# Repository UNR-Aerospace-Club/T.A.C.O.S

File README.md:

# T.A.C.O.S
Typical Avionics Control and Operations System

The hardware and software needed for a custom hat-based modular rocket avionics system

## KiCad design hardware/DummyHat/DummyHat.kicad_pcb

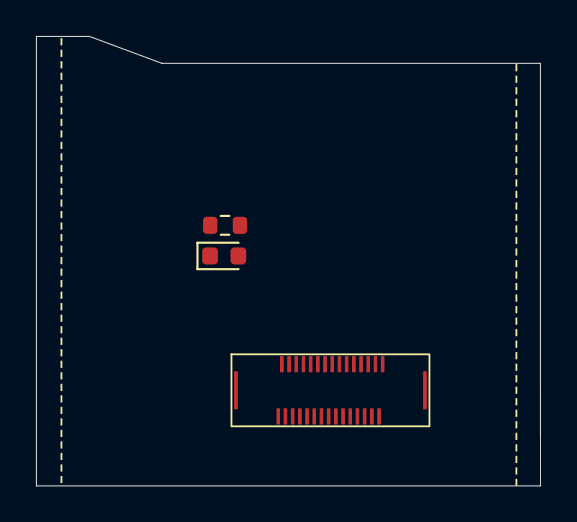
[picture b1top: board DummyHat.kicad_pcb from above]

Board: 2 copper layers, 28.0 x 25.0 mm, 4 parts (1 on the bottom side), 33 nets, no tracks yet.

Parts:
D1: LED; LED_0603_1608Metric
J1, J2: Conn_02x16_Top_Bottom; FSB5 Series 0.40 mm Pitch Floating SlimStack Board-to-Board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
R1: R; R_0603_1608Metric

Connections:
CONN_0: D1.2 (A), J1.1, J2.16
CONN_1: J1.2, J2.17
CONN_2: J1.3, J2.18
CONN_3: J1.4, J2.19
CONN_4: J1.5, J2.20
CONN_5: J1.6, J2.21
CONN_6: J1.7, J2.22
CONN_7: J1.8, J2.23
CONN_8: J1.9, J2.24
CONN_9: J1.10, J2.25
CONN_10: J1.11, J2.26
CONN_11: J1.12, J2.27
CONN_12: J1.13, J2.28
CONN_13: J1.14, J2.29
CONN_14: J1.15, J2.30
CONN_15: J1.16, J2.1
CONN_16: J1.17, J2.2
CONN_17: J1.18, J2.3
CONN_18: J1.19, J2.4
CONN_19: J1.20, J2.5
CONN_20: J1.21, J2.6
CONN_21: J1.22, J2.7
CONN_22: J1.23, J2.8
CONN_23: J1.24, J2.9
CONN_24: J1.25, J2.10
CONN_25: J1.26, J2.11
CONN_26: J1.27, J2.12
CONN_27: J1.28, J2.13
CONN_28: J1.29, J2.14
CONN_29: J1.30, J2.15
GND: J1.32, J2.32, R1.1
unnamed: D1.1 (K), R1.2
VIN: J1.31, J2.31

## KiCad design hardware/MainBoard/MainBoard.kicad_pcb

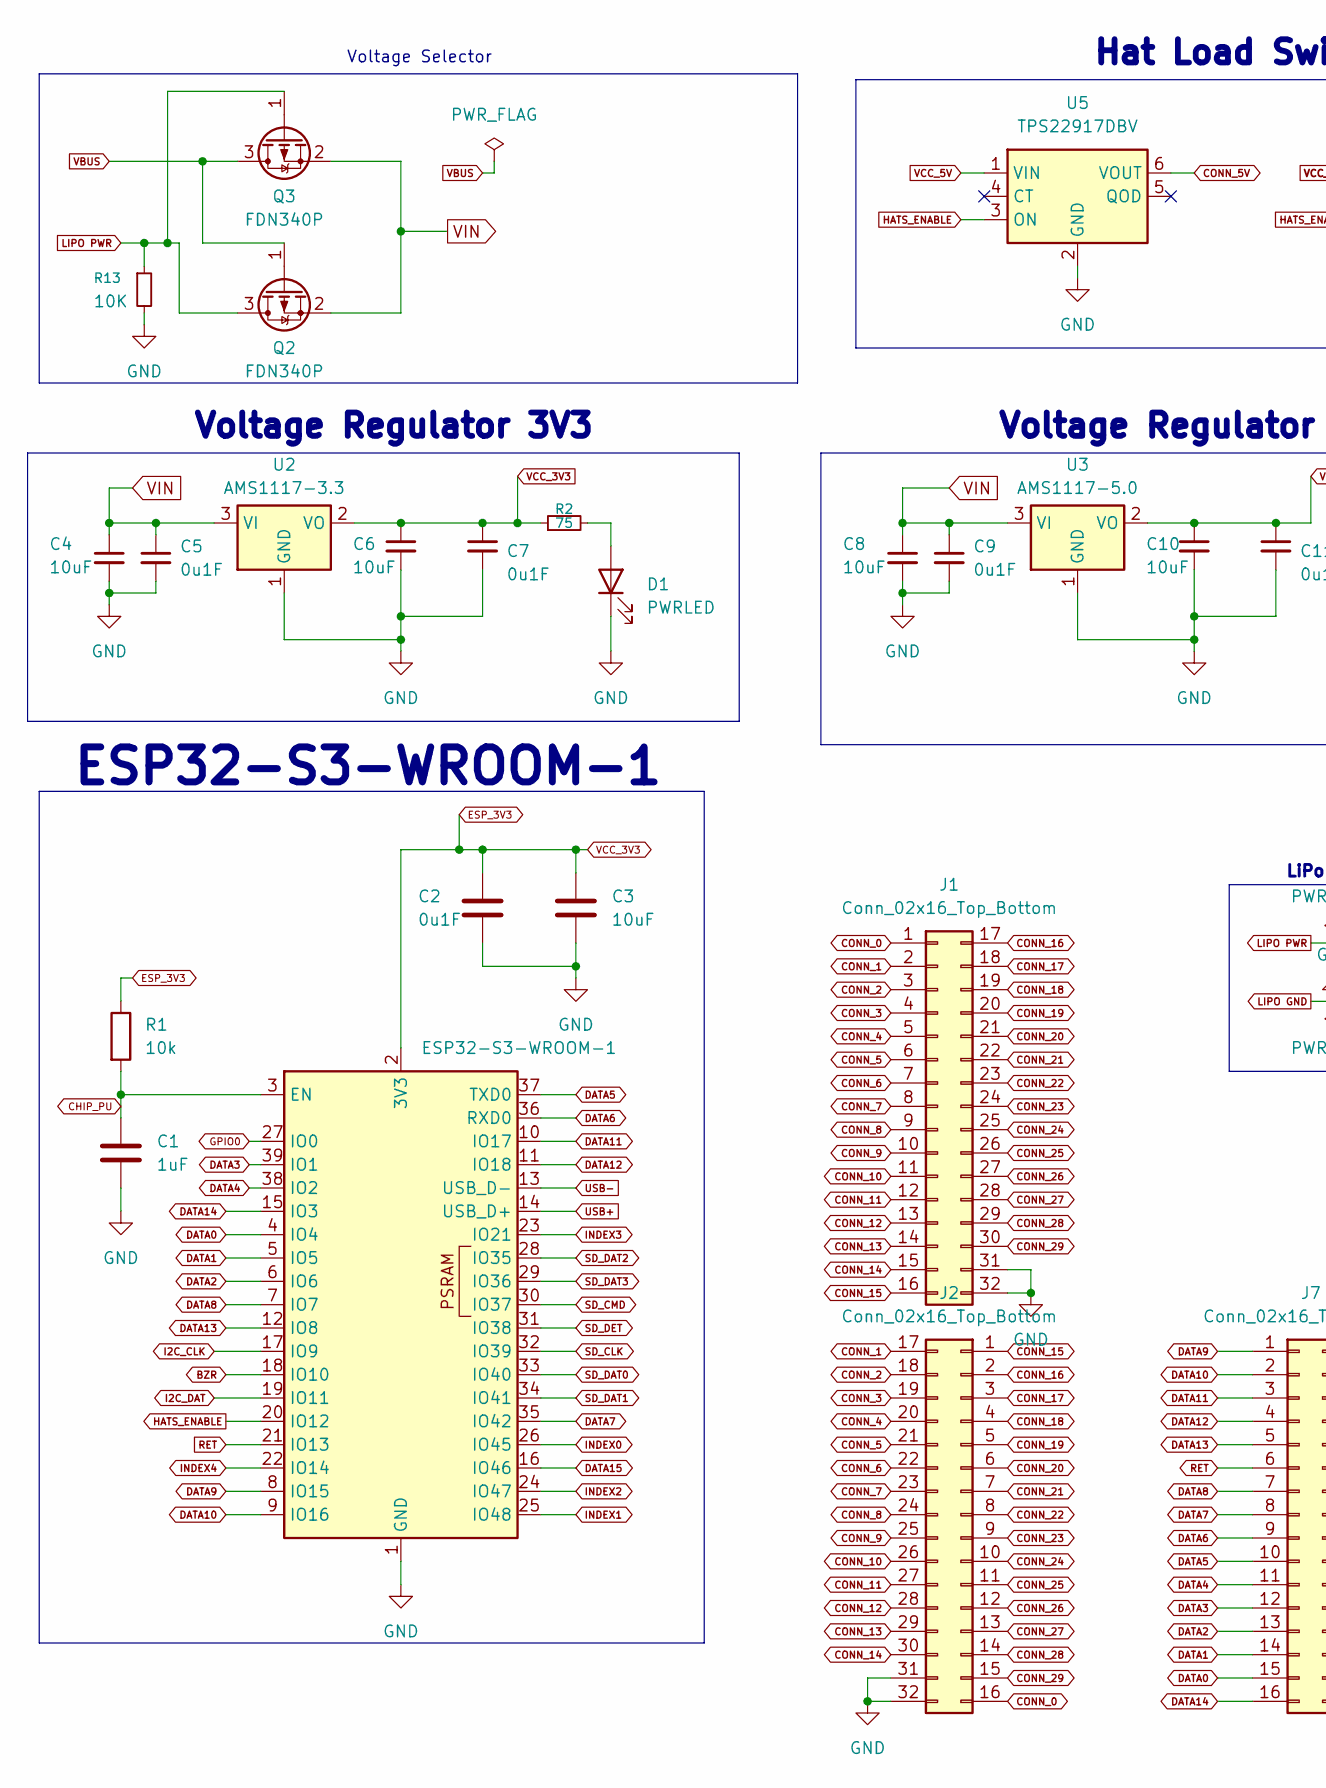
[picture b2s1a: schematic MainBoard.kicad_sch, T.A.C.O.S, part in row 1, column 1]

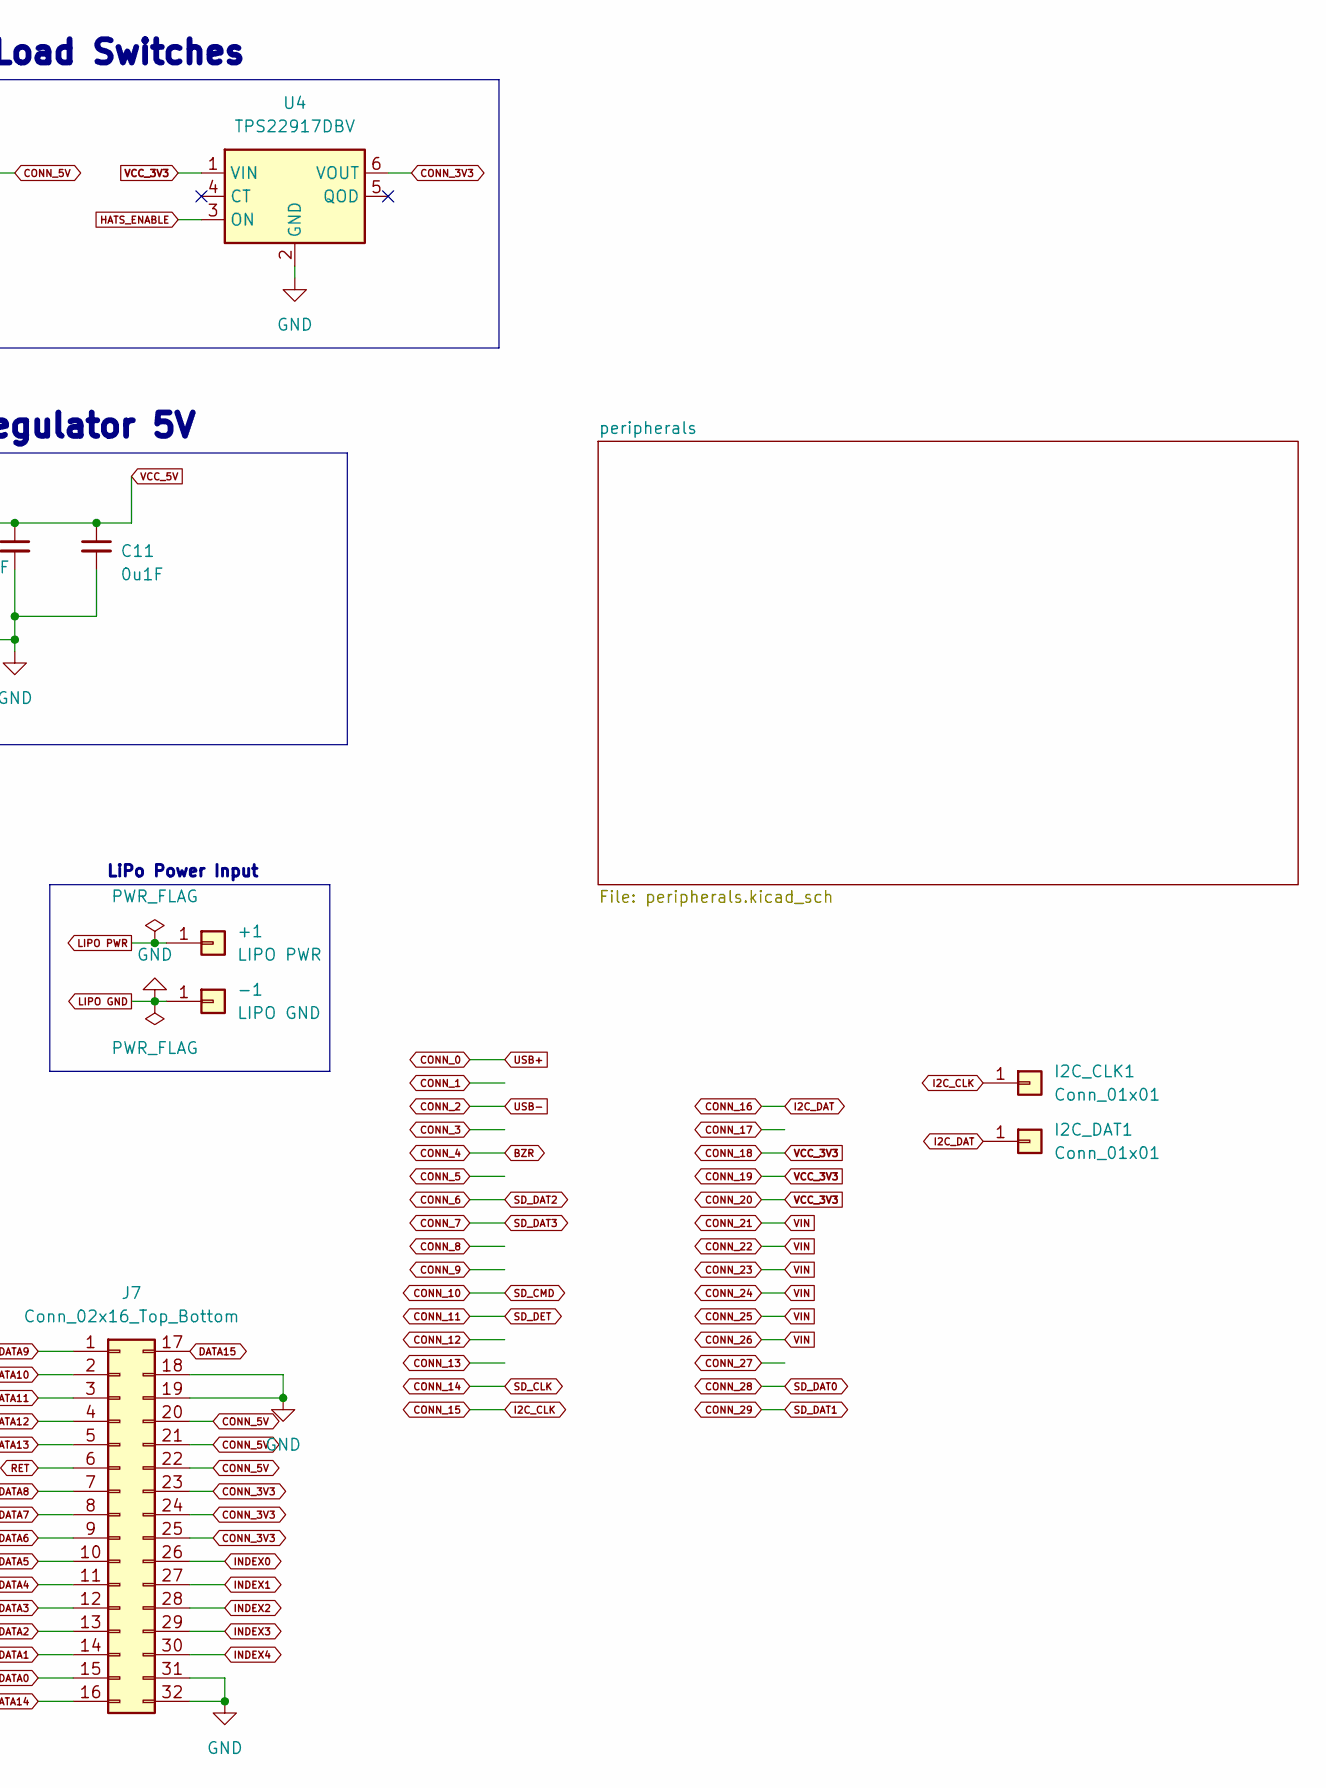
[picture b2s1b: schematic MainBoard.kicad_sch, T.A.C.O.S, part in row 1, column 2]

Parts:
+1: LIPO PWR; TestPoint_Pad_2.0x2.0mm
-1: LIPO GND; TestPoint_Pad_2.0x2.0mm
C1: 1uF; C_0603_1608Metric
C2, C5, C7, C9, C11: 0u1F; C_0402_1005Metric
C3, C4, C6, C8, C10: 10uF; C_0603_1608Metric
D1: PWRLED; LED_0603_1608Metric
I2C_CLK1, I2C_DAT1: Conn_01x01; TestPoint_Pad_1.0x1.0mm
J1, J2, J7: Conn_02x16_Top_Bottom; FSB5 Series 0.40 mm Pitch Floating SlimStack Board-to-Board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
Q2, Q3: FDN340P; SOT-23
R1: 10k; R_0603_1608Metric
R2: 75; R_0603_1608Metric
R13: 10K; R_0603_1608Metric
U1: ESP32-S3-WROOM-1; ESP32-S3-WROOM-1U
U2: AMS1117-3.3; SOT-223-3_TabPin2
U3: AMS1117-5.0; SOT-223-3_TabPin2
U4, U5: TPS22917DBV; SOT-23-6

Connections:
BZR: J1.5, J2.20, U1.18 (IO10); also elsewhere on the board
CHIP_PU: C1.1, R1.2, U1.3 (EN); also elsewhere on the board
CONN_0: J1.1, J2.16, U1.14 (USB_D+); also elsewhere on the board
CONN_1: J1.2, J2.17
CONN_2: J1.3, J2.18, U1.13 (USB_D-); also elsewhere on the board
CONN_3: J1.4, J2.19
CONN_3V3: J7.23, J7.24, J7.25, U4.6 (VOUT)
CONN_5: J1.6, J2.21
CONN_5V: J7.20, J7.21, J7.22, U5.6 (VOUT)
CONN_6: J1.7, J2.22, U1.28 (IO35); also elsewhere on the board
CONN_7: J1.8, J2.23, U1.29 (IO36); also elsewhere on the board
CONN_8: J1.9, J2.24
CONN_9: J1.10, J2.25
CONN_10: J1.11, J2.26, U1.30 (IO37); also elsewhere on the board
CONN_11: J1.12, J2.27, U1.31 (IO38); also elsewhere on the board
CONN_12: J1.13, J2.28
CONN_13: J1.14, J2.29
CONN_14: J1.15, J2.30, U1.32 (IO39); also elsewhere on the board
CONN_15: I2C_CLK1.1, J1.16, J2.1, U1.17 (IO9)
CONN_16: I2C_DAT1.1, J1.17, J2.2, U1.19 (IO11)
CONN_17: J1.18, J2.3
CONN_18: C2.1, C3.1, C6.1, C7.1, J1.19, J1.20, J1.21, J2.4, J2.5, J2.6, R1.1, R2.1, U1.2 (3V3), U2.2 (VO), U4.1 (VIN); also elsewhere on the board
CONN_21: C4.1, C5.1, C8.1, C9.1, J1.22, J1.23, J1.24, J1.25, J1.26, J1.27, J2.7, J2.8, J2.9, J2.10, J2.11, J2.12, Q2.2 (S), Q3.2 (S), U2.3 (VI), U3.3 (VI)
CONN_27: J1.28, J2.13
CONN_28: J1.29, J2.14, U1.33 (IO40); also elsewhere on the board
CONN_29: J1.30, J2.15, U1.34 (IO41); also elsewhere on the board
DATA0: J7.15, U1.4 (IO4)
DATA1: J7.14, U1.5 (IO5)
DATA2: J7.13, U1.6 (IO6)
DATA3: J7.12, U1.39 (IO1)
DATA4: J7.11, U1.38 (IO2)
DATA5: J7.10, U1.37 (TXD0)
DATA6: J7.9, U1.36 (RXD0)
DATA7: J7.8, U1.35 (IO42)
DATA8: J7.7, U1.7 (IO7)
DATA9: J7.1, U1.8 (IO15)
DATA10: J7.2, U1.9 (IO16)
DATA11: J7.3, U1.10 (IO17)
DATA12: J7.4, U1.11 (IO18)
DATA13: J7.5, U1.12 (IO8)
DATA14: J7.16, U1.15 (IO3)
DATA15: J7.17, U1.16 (IO46)
GPIO0: U1.27 (IO0); also elsewhere on the board
HATS_ENABLE: U1.20 (IO12), U4.3 (ON), U5.3 (ON)
INDEX0: J7.26, U1.26 (IO45)
INDEX1: J7.27, U1.25 (IO48)
INDEX2: J7.28, U1.24 (IO47)
INDEX3: J7.29, U1.23 (IO21)
INDEX4: J7.30, U1.22 (IO14)
LIPO GND: -1.1, C1.2, C2.2, C3.2, C4.2, C5.2, C6.2, C7.2, C8.2, C9.2, C10.2, C11.2, D1.1 (K), J1.31, J1.32, J2.31, J2.32, J7.18, J7.19, J7.31, J7.32, R13.2, U1.1 (GND), U1.40 (GND), U1.41 (GND), U2.1 (GND), U3.1 (GND), U4.2 (GND), U5.2 (GND); also elsewhere on the board
LIPO PWR: +1.1, Q2.3 (D), Q3.1 (G), R13.1
unnamed: D1.2 (A), R2.2
RET: J7.6, U1.21 (IO13)
VBUS: Q2.1 (G), Q3.3 (D); also elsewhere on the board
VCC_5V: C10.1, C11.1, U3.2 (VO), U5.1 (VIN)

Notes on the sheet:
Voltage Regulator 5V
ESP32-S3-WROOM-1
Voltage Regulator 3V3
Voltage Selector
LiPo Power Input
Hat Load Switches

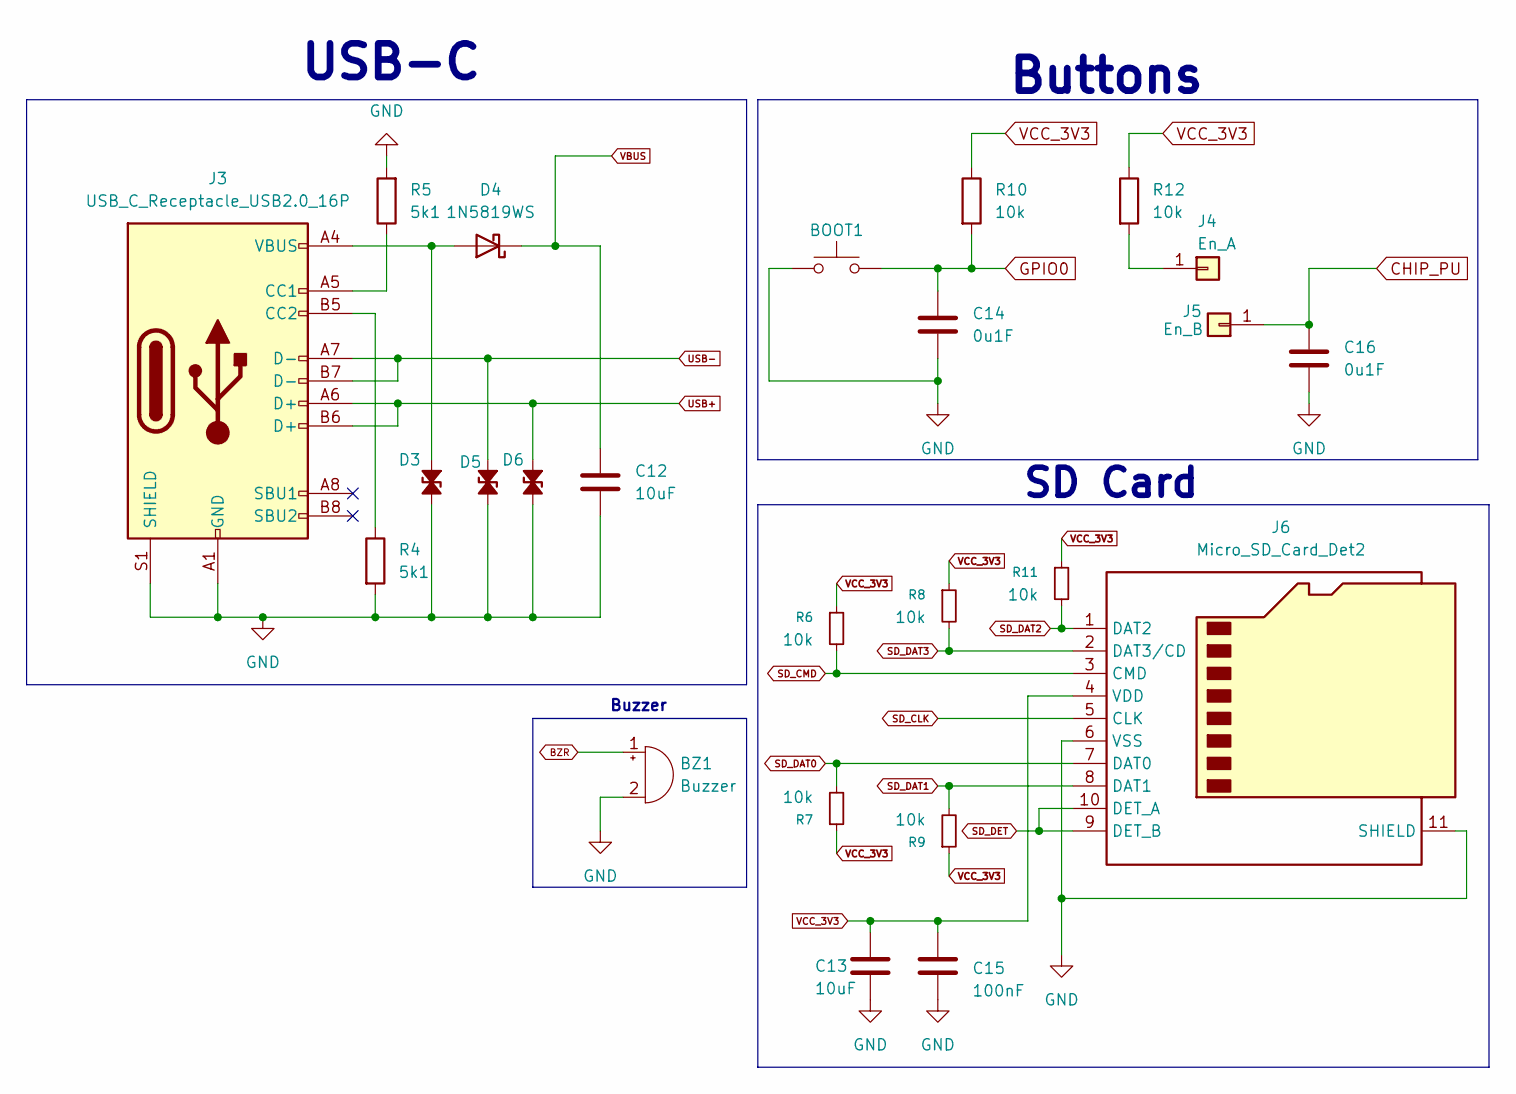
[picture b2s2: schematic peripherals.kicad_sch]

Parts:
BOOT1: RESET; SW_Push_1P1T_NO_CK_KMR2
BZ1: Buzzer; Buzzer_Murata_PKMCS0909E
C12, C13: 10uF; C_0603_1608Metric
C14, C16: 0u1F; C_0402_1005Metric
C15: 100nF; C_0402_1005Metric
D3, D5, D6: D_TVS_Small_Filled; D_0603_1608Metric
D4: 1N5819WS; D_SOD-323
J3: USB_C_Receptacle_USB2.0_16P; USB_C_Receptacle_GCT_USB4085
J4: En_A; TestPoint_Pad_1.5x1.5mm
J5: En_B; TestPoint_Pad_1.5x1.5mm
J6: Micro_SD_Card_Det2; microSD_HC_Hirose_DM3AT-SF-PEJM5
R4, R5: 5k1; R_0402_1005Metric
R6, R7, R8, R9, R10, R11, R12: 10k; R_0603_1608Metric

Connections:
BZR: BZ1.1 (+); also elsewhere on the board
CHIP_PU: C16.1, J5.1; also elsewhere on the board
CONN_0: D6.1 (A1), J3.A6 (D+), J3.B6 (D+); also elsewhere on the board
CONN_2: D5.1 (A1), J3.A7 (D-), J3.B7 (D-); also elsewhere on the board
CONN_6: J6.1 (DAT2), R11.2; also elsewhere on the board
CONN_7: J6.2 (DAT3/CD), R8.2; also elsewhere on the board
CONN_10: J6.3 (CMD), R6.2; also elsewhere on the board
CONN_11: J6.9 (DET_B), J6.10 (DET_A); also elsewhere on the board
CONN_14: J6.5 (CLK); also elsewhere on the board
CONN_18: C13.1, C15.1, J6.4 (VDD), R6.1, R7.1, R8.1, R9.1, R10.1, R11.1, R12.1; also elsewhere on the board
CONN_28: J6.7 (DAT0), R7.2; also elsewhere on the board
CONN_29: J6.8 (DAT1), R9.2; also elsewhere on the board
GPIO0: BOOT1.2, C14.1, R10.2; also elsewhere on the board
LIPO GND: BOOT1.1, BZ1.2 (-), C12.2, C13.2, C14.2, C15.2, C16.2, D3.2 (A2), D5.2 (A2), D6.2 (A2), J3.A1 (GND), J3.A12 (GND), J3.B1 (GND), J3.B12 (GND), J3.S1 (SHIELD), J6.6 (VSS), J6.11 (SHIELD), R4.2, R5.2; also elsewhere on the board
unnamed: D3.1 (A1), D4.2 (A), J3.A4 (VBUS), J3.A9 (VBUS), J3.B4 (VBUS), J3.B9 (VBUS)
unnamed: J3.A5 (CC1), R5.1
unnamed: J3.B5 (CC2), R4.1
unnamed: J4.1, R12.2
VBUS: C12.1, D4.1 (K); also elsewhere on the board

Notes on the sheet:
USB-C
Buzzer
SD Card
Buttons

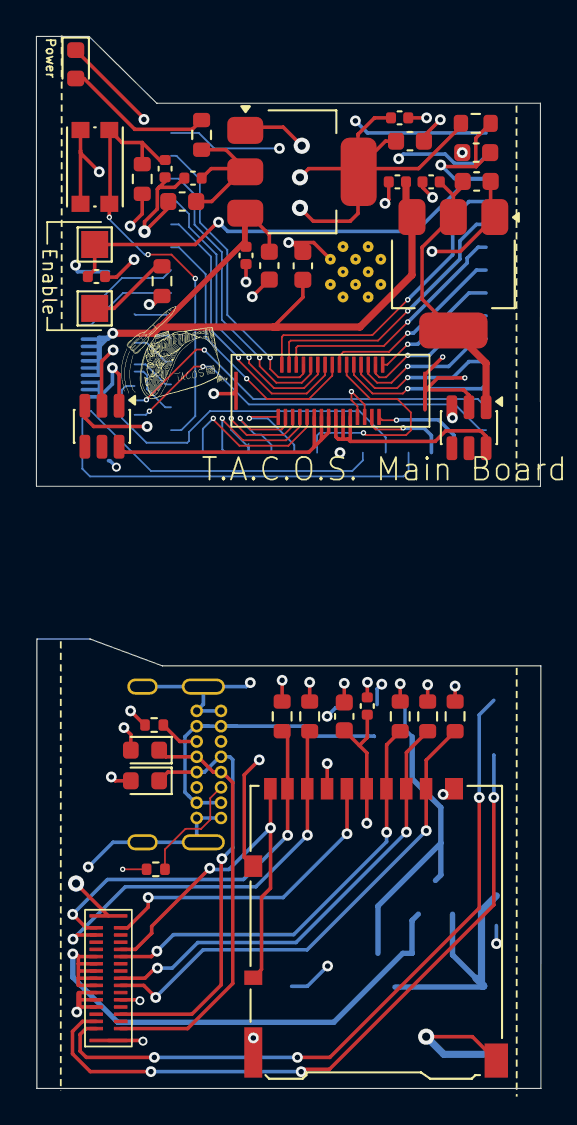
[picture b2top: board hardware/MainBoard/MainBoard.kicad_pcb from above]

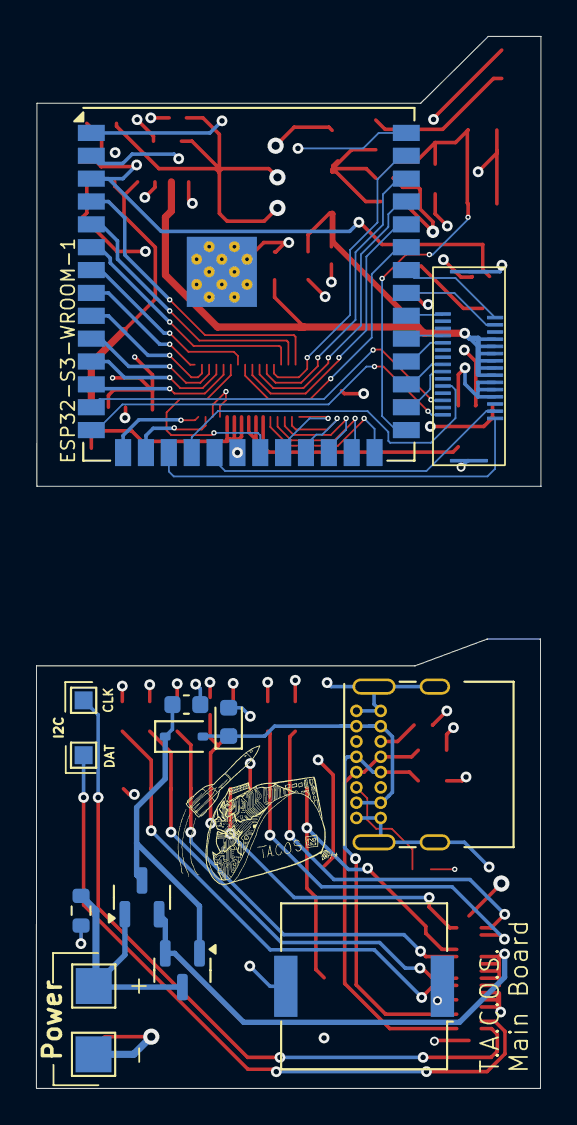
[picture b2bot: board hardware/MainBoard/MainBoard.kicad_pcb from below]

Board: 4 copper layers, 28.0 x 58.4 mm, 53 parts (14 on the bottom side), 59 nets.

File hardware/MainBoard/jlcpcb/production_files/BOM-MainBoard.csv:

Comment,Designator,Footprint,LCSC,Quantity
10uF,C13,C_0603_1608Metric,,1
10uF,C8,C_0603_1608Metric,,1
Conn_02x16_Top_Bottom,J1,FSB5 Series 0.40 mm Pitch Floating SlimStack Board-to-Board Receptacles,,1
0u1F,C16,C_0402_1005Metric,,1
10k,R7,R_0603_1608Metric,,1
10k,R11,R_0603_1608Metric,,1
0u1F,C14,C_0402_1005Metric,,1
PWRLED,D1,LED_0603_1608Metric,,1
10k,R6,R_0603_1608Metric,,1
10uF,C3,C_0603_1608Metric,,1
En_B,J5,TestPoint_Pad_1.5x1.5mm,,1
0u1F,C11,C_0402_1005Metric,,1
Conn_02x16_Top_Bottom,J7,FSB5 Series 0.40 mm Pitch Floating SlimStack Board-to-Board Plugs,,1
10uF,C6,C_0603_1608Metric,,1
10k,R10,R_0603_1608Metric,,1
10k,R12,R_0603_1608Metric,,1
10k,R1,R_0603_1608Metric,,1
1uF,C1,C_0603_1608Metric,,1
TPS22917DBV,U5,SOT-23-6,,1
Micro_SD_Card_Det2,J6,microSD_HC_Hirose_DM3AT-SF-PEJM5,,1
D_TVS_Small_Filled,D6,D_0603_1608Metric,,1
AMS1117-5.0,U3,SOT-223-3_TabPin2,,1
0u1F,C7,C_0402_1005Metric,,1
10uF,C10,C_0603_1608Metric,,1
0u1F,C2,C_0402_1005Metric,,1
D_TVS_Small_Filled,D5,D_0603_1608Metric,,1
5k1,R5,R_0402_1005Metric,,1
5k1,R4,R_0402_1005Metric,,1
75,R2,R_0603_1608Metric,,1
RESET,BOOT1,SW_Push_1P1T_NO_CK_KMR2,,1
100nF,C15,C_0402_1005Metric,,1
0u1F,C5,C_0402_1005Metric,,1
0u1F,C9,C_0402_1005Metric,,1
En_A,J4,TestPoint_Pad_1.5x1.5mm,,1
TPS22917DBV,U4,SOT-23-6,,1
AMS1117-3.3,U2,SOT-223-3_TabPin2,,1
10k,R9,R_0603_1608Metric,,1
10k,R8,R_0603_1608Metric,,1
10uF,C4,C_0603_1608Metric,,1
FDN340P,Q3,SOT-23,,1
1N5819WS,D4,D_SOD-323,,1
LIPO GND,-1,TestPoint_Pad_2.0x2.0mm,,1
ESP32-S3-WROOM-1,U1,ESP32-S3-WROOM-1U,,1
10K,R13,R_0603_1608Metric,,1
D_TVS_Small_Filled,D3,D_0603_1608Metric,,1
USB_C_Receptacle_USB2.0_16P,J3,USB_C_Receptacle_GCT_USB4085,,1
FDN340P,Q2,SOT-23,,1
10uF,C12,C_0603_1608Metric,,1
Buzzer,BZ1,Buzzer_Murata_PKMCS0909E,,1
Conn_02x16_Top_Bottom,J2,FSB5 Series 0.40 mm Pitch Floating SlimStack Board-to-Board Plugs,,1

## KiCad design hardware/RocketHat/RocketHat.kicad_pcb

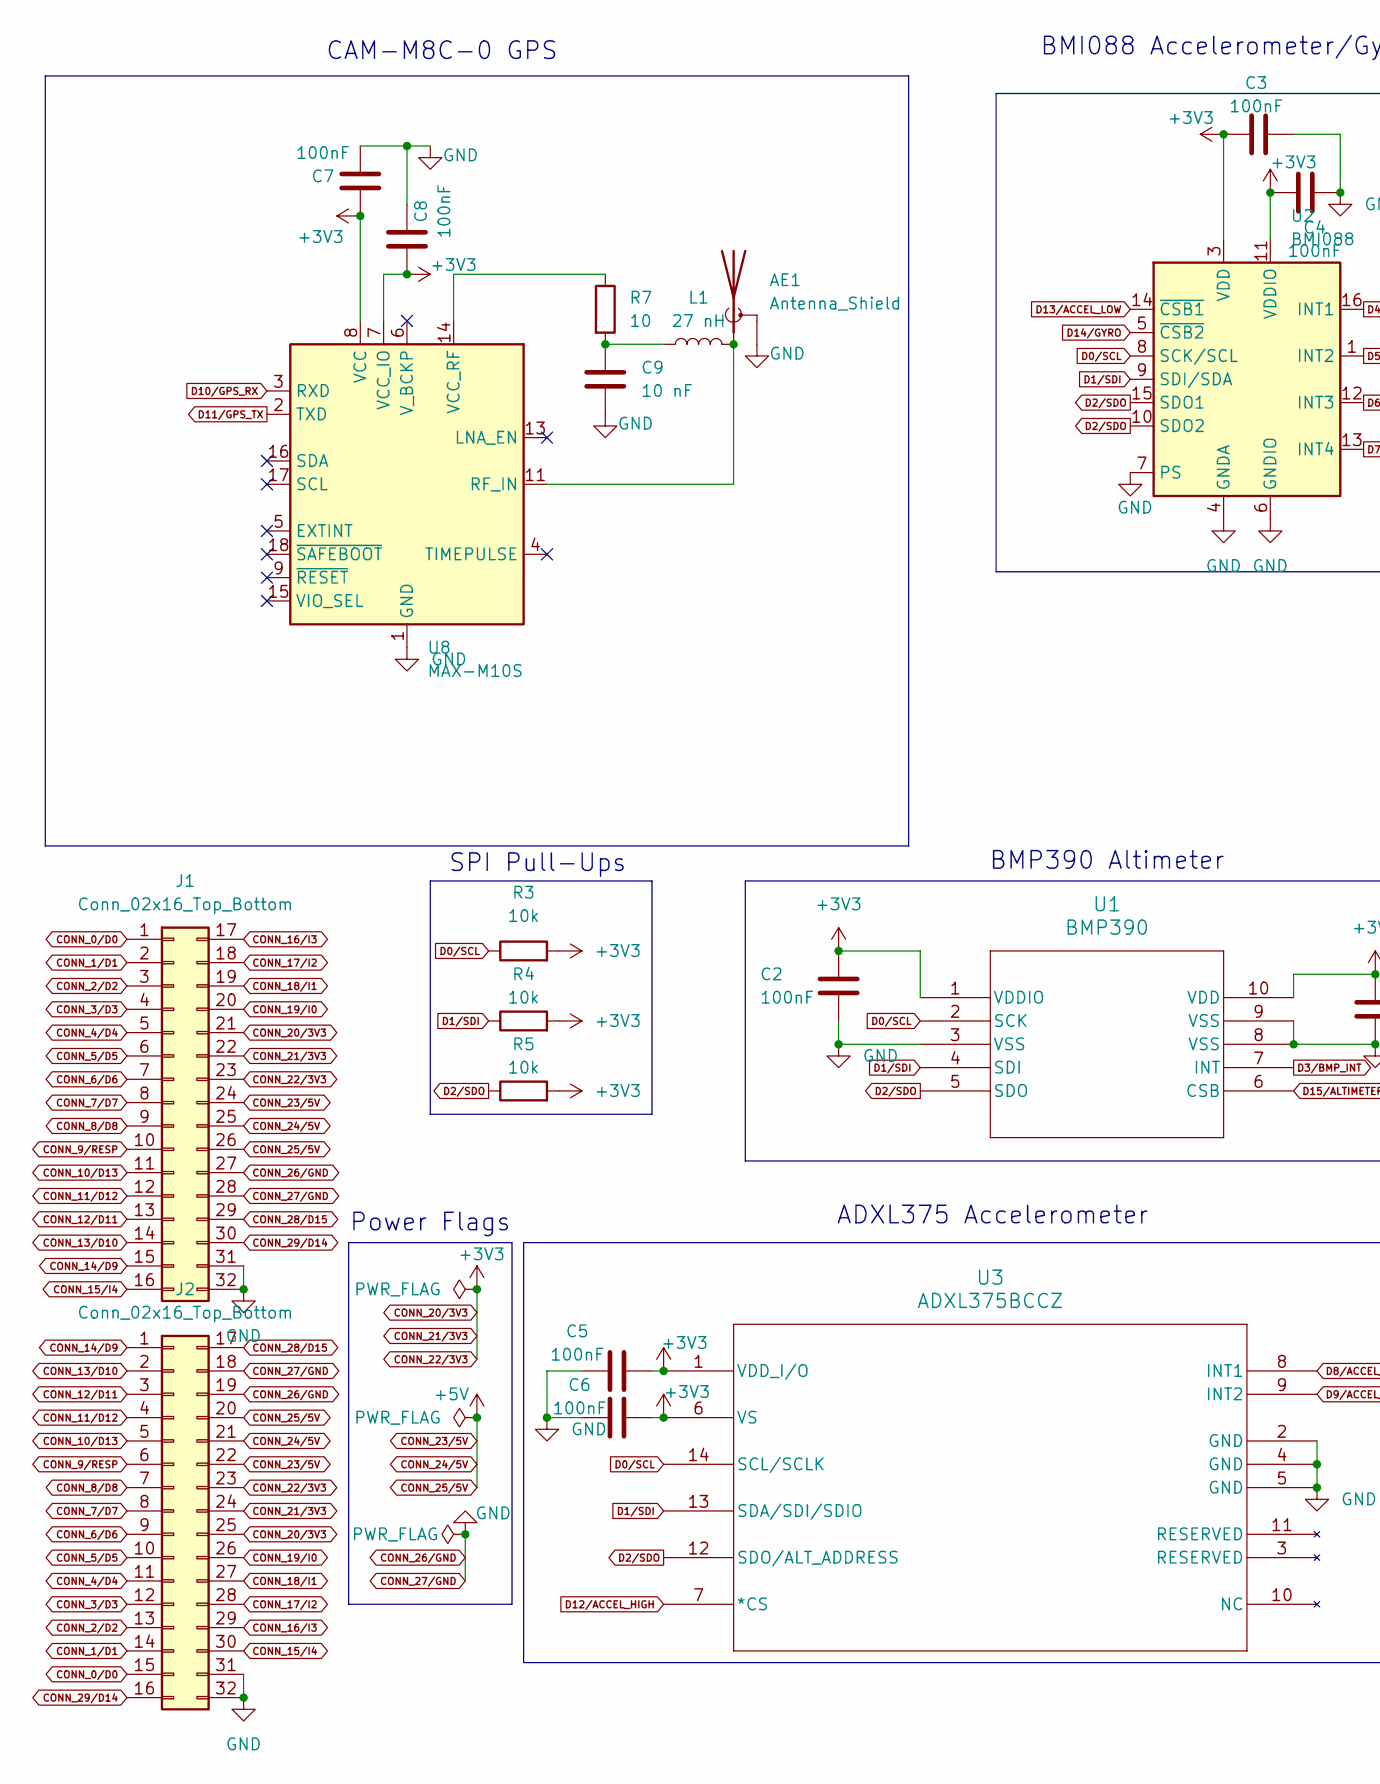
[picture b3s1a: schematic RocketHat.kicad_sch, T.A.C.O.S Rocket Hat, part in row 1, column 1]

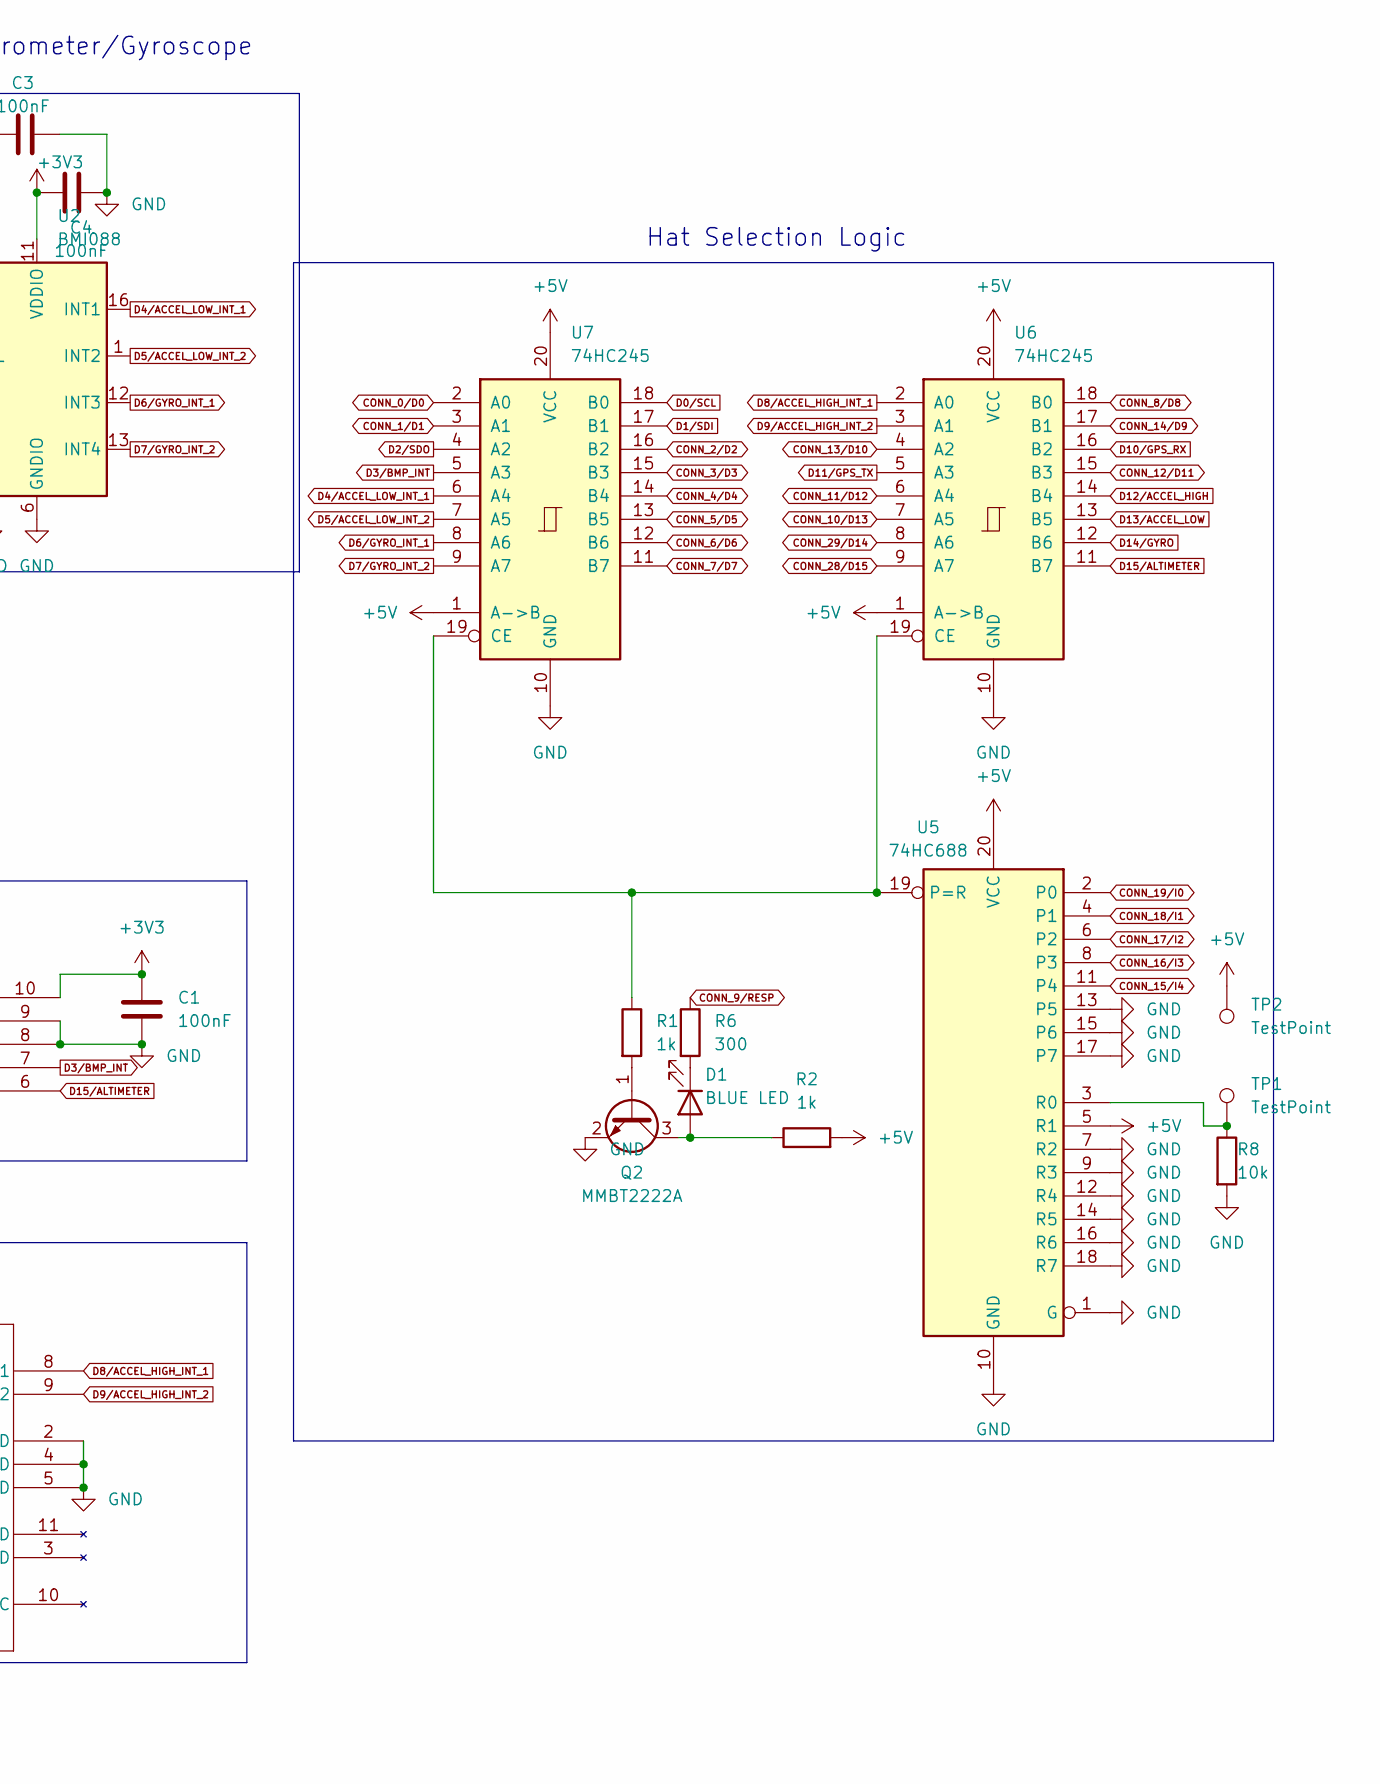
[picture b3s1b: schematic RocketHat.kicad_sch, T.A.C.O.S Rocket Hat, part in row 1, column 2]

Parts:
AE1: Antenna_Shield; U.FL_Molex_MCRF_73412-0110_Vertical
C1, C2, C3, C4, C5, C6, C7, C8: 100nF; C_0201_0603Metric
C9: 10 nF; C_0201_0603Metric
D1: BLUE LED; LED_0201_0603Metric
J1, J2: Conn_02x16_Top_Bottom; FSB5 Series 0.40 mm Pitch Floating SlimStack Board-to-Board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
L1: 27 nH; L_0201_0603Metric
Q2: MMBT2222A; SOT-23
R1, R2: 1k; R_0201_0603Metric
R3, R4, R5, R8: 10k; R_0201_0603Metric
R6: 300; R_0201_0603Metric
R7: 10; R_0201_0603Metric
TP1, TP2: TestPoint; TestPoint_Pad_1.5x1.5mm
U1: BMP390; 10LGA_2X2X0p75_BOS
U2: BMI088; Bosch_LGA-16_4.5x3mm_P0.5mm_LayoutBorder7x1y_ClockwisePinNu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
U3: ADXL375BCCZ; LGA_CC-14-1_ADI
U5: 74HC688; TSSOP-20_4.4x6.5mm_P0.65mm
U6, U7: 74HC245; DHVQFN-20-1EP_2.5x4.5mm_P0.5mm_EP1x3mm
U8: MAX-M10S; ublox_MAX

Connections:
CONN_0/D0: J1.1, J2.15, U7.2 (A0)
CONN_1/D1: J1.2, J2.14, U7.3 (A1)
CONN_2/D2: J1.3, J2.13, U7.16 (B2)
CONN_3/D3: J1.4, J2.12, U7.15 (B3)
CONN_4/D4: J1.5, J2.11, U7.14 (B4)
CONN_5/D5: J1.6, J2.10, U7.13 (B5)
CONN_6/D6: J1.7, J2.9, U7.12 (B6)
CONN_7/D7: J1.8, J2.8, U7.11 (B7)
CONN_8/D8: J1.9, J2.7, U6.18 (B0)
CONN_9/RESP: J1.10, J2.6, R6.1
CONN_10/D13: J1.11, J2.5, U6.7 (A5)
CONN_11/D12: J1.12, J2.4, U6.6 (A4)
CONN_12/D11: J1.13, J2.3, U6.15 (B3)
CONN_13/D10: J1.14, J2.2, U6.4 (A2)
CONN_14/D9: J1.15, J2.1, U6.17 (B1)
CONN_15/I4: J1.16, J2.30, U5.11 (P4)
CONN_16/I3: J1.17, J2.29, U5.8 (P3)
CONN_17/I2: J1.18, J2.28, U5.6 (P2)
CONN_18/I1: J1.19, J2.27, U5.4 (P1)
CONN_19/I0: J1.20, J2.26, U5.2 (P0)
CONN_20/3V3: C1.1, C2.1, C3.2, C4.2, C5.1, C6.1, C7.2, C8.2, J1.21, J1.22, J1.23, J2.23, J2.24, J2.25, R3.2, R4.2, R5.2, U1.1 (VDDIO), U1.10 (VDD), U2.3 (VDD), U2.11 (VDDIO), U3.1 (VDD_I/O), U3.6 (VS), U8.7 (VCC_IO), U8.8 (VCC)
CONN_23/5V: J1.24, J1.25, J1.26, J2.20, J2.21, J2.22, R2.2, TP2.1, U5.5 (R1), U5.20 (VCC), U6.1 (A->B), U6.20 (VCC), U7.1 (A->B), U7.20 (VCC)
CONN_26/GND: AE1.2 (Shield), C1.2, C2.2, C3.1, C4.1, C5.2, C6.2, C7.1, C8.1, C9.2, J1.27, J1.28, J1.31, J1.32, J2.18, J2.19, J2.31, J2.32, Q2.2 (E), R8.2, U1.3 (VSS), U1.8 (VSS), U1.9 (VSS), U2.2 (GNDA), U2.4 (GNDA), U2.6 (GNDIO), U2.7 (PS), U3.2 (GND), U3.4 (GND), U3.5 (GND), U5.1 (G), U5.7 (R2), U5.9 (R3), U5.10 (GND), U5.12 (R4), U5.13 (P5), U5.14 (R5), U5.15 (P6), U5.16 (R6), U5.17 (P7), U5.18 (R7), U6.10 (GND), U6.21, U7.10 (GND), U7.21, U8.1 (GND), U8.10 (GND), U8.12 (GND)
CONN_28/D15: J1.29, J2.17, U6.9 (A7)
CONN_29/D14: J1.30, J2.16, U6.8 (A6)
D0/SCL: R3.1, U1.2 (SCK), U2.8 (SCK/SCL), U3.14 (SCL/SCLK), U7.18 (B0)
D1/SDI: R4.1, U1.4 (SDI), U2.9 (SDI/SDA), U3.13 (SDA/SDI/SDIO), U7.17 (B1)
D2/SDO: R5.1, U1.5 (SDO), U2.10 (SDO2), U2.15 (SDO1), U3.12 (SDO/ALT_ADDRESS), U7.4 (A2)
D3/BMP_INT: U1.7 (INT), U7.5 (A3)
D4/ACCEL_LOW_INT_1: U2.16 (INT1), U7.6 (A4)
D5/ACCEL_LOW_INT_2: U2.1 (INT2), U7.7 (A5)
D6/GYRO_INT_1: U2.12 (INT3), U7.8 (A6)
D7/GYRO_INT_2: U2.13 (INT4), U7.9 (A7)
D8/ACCEL_HIGH_INT_1: U3.8 (INT1), U6.2 (A0)
D9/ACCEL_HIGH_INT_2: U3.9 (INT2), U6.3 (A1)
D10/GPS_RX: U6.16 (B2), U8.3 (RXD)
D11/GPS_TX: U6.5 (A3), U8.2 (TXD)
D12/ACCEL_HIGH: U3.7 (*CS), U6.14 (B4)
D13/ACCEL_LOW: U2.14 (~CSB1), U6.13 (B5)
D14/GYRO: U2.5 (~CSB2), U6.12 (B6)
D15/ALTIMETER: U1.6 (CSB), U6.11 (B7)
unnamed: AE1.1 (A), L1.2, U8.11 (RF_IN)
unnamed: C9.1, L1.1, R7.2
unnamed: D1.2 (A), Q2.3 (C), R2.1
unnamed: D1.1 (K), R6.2
unnamed: Q2.1 (B), R1.2
unnamed: R1.1, U5.19 (P=R), U6.19 (CE), U7.19 (CE)
unnamed: R8.1, TP1.1, U5.3 (R0)
unnamed: R7.1, U8.14 (VCC_RF)

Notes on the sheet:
SPI Pull-Ups
Hat Selection Logic
CAM-M8C-0 GPS
BMP390 Altimeter
Power Flags
ADXL375 Accelerometer
BMI088 Accelerometer/Gyroscope

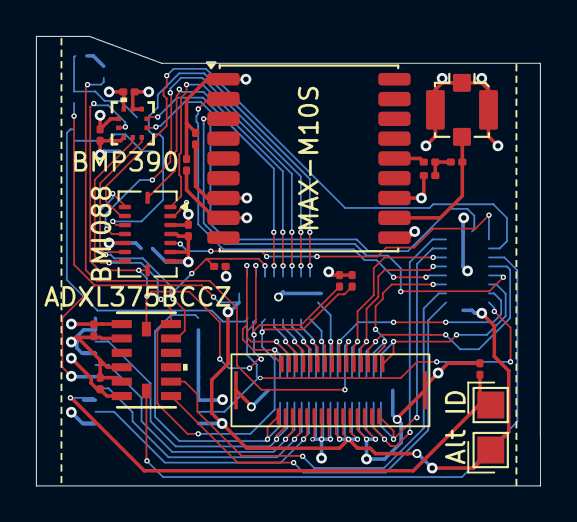
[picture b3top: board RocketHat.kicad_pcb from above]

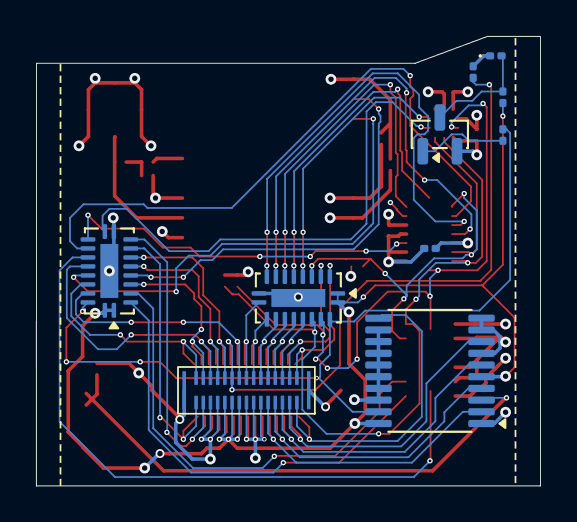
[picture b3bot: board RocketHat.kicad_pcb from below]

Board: 4 copper layers, 28.0 x 25.0 mm, 32 parts (10 on the bottom side), 49 nets.
